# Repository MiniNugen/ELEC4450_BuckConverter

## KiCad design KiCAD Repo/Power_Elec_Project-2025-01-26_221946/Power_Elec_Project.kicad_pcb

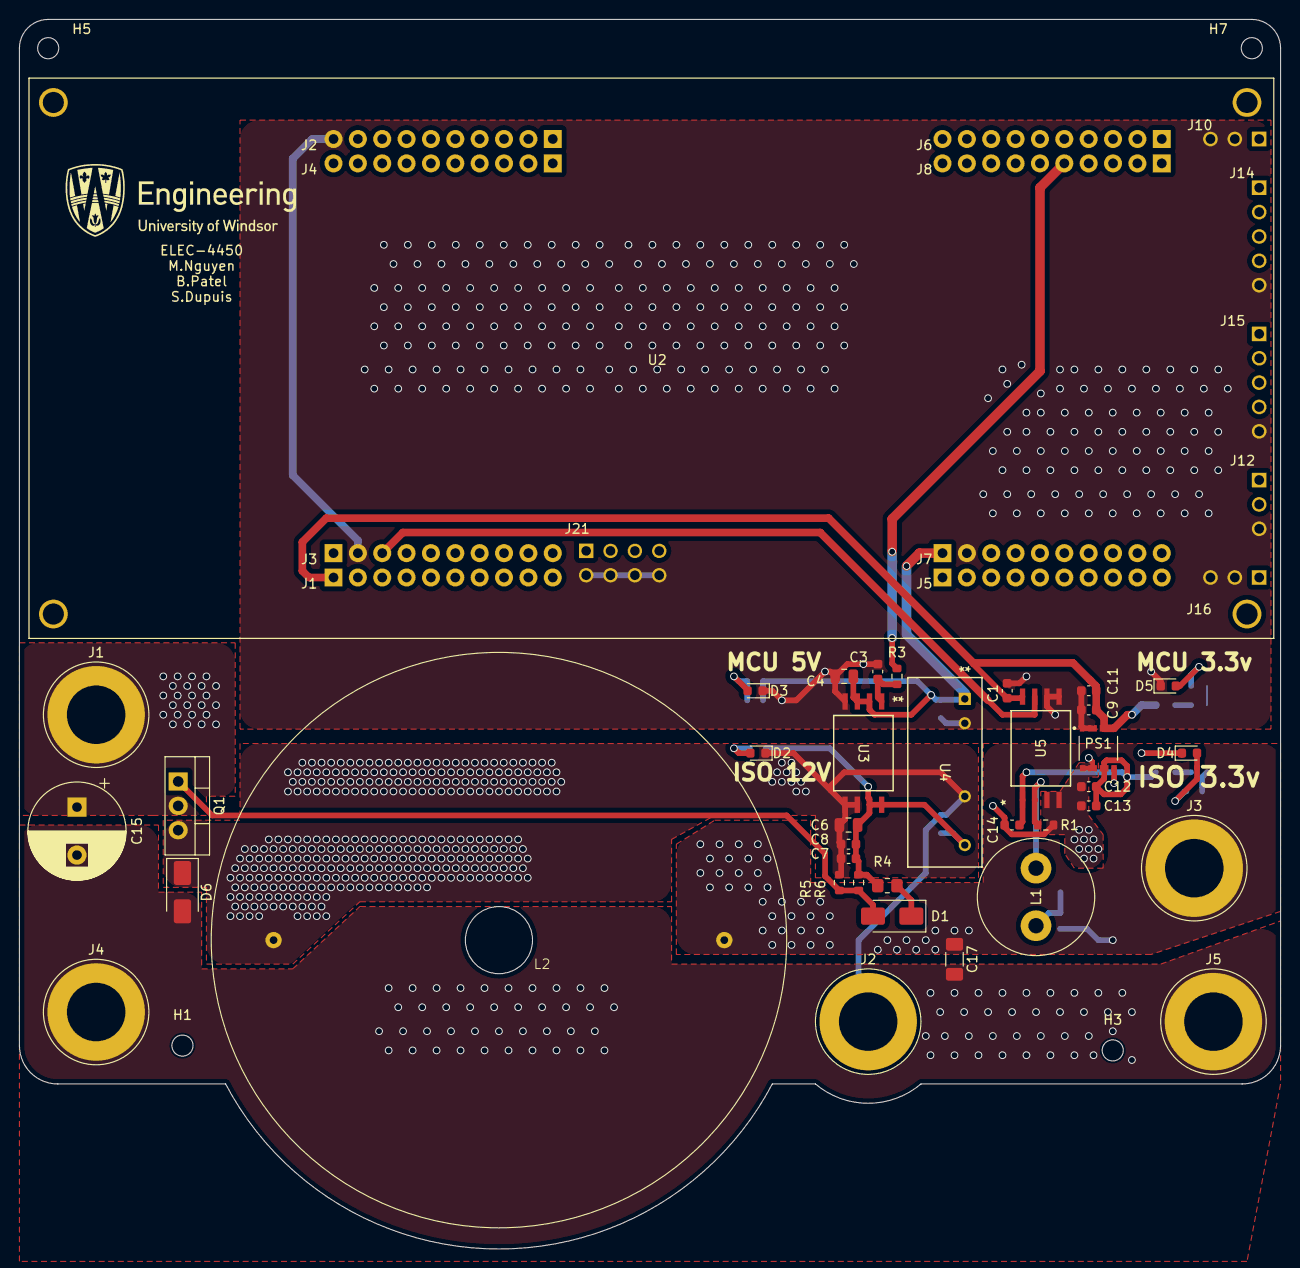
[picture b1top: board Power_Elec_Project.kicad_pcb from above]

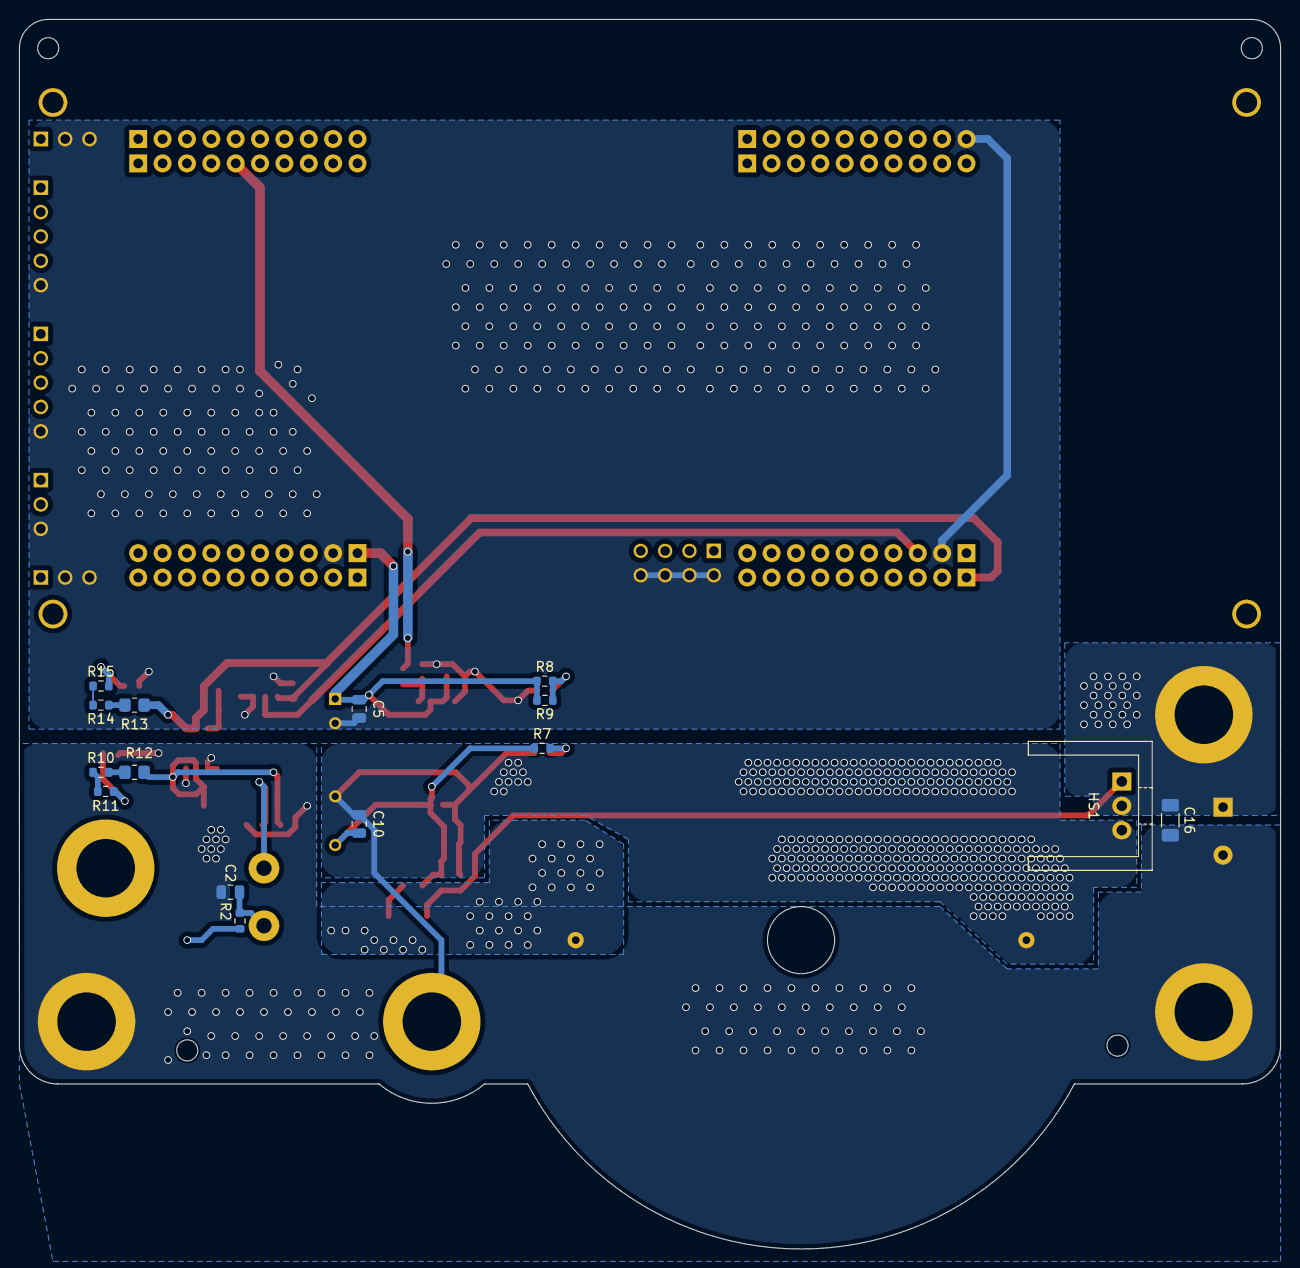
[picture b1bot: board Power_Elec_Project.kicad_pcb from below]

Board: 2 copper layers, 131.5 x 128.2 mm, 56 parts (15 on the bottom side), 24 nets.

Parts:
C1, C9, C12, C14: 0.1uF; C_0603_1608Metric
C2, C5, C10: 1.5 µF; C_0805_2012Metric
C3: 33pF; C_0603_1608Metric
C4, C6: 2.2uF; C_0805_2012Metric
C7, C8, C11: 10uF; C_0603_1608Metric
C13: 22uF; C_0603_1608Metric
C15: 470uF; CP_Radial_D10.0mm_P5.00mm
C16: 1uF; C_1206_3216Metric_Pad1.33x1.80mm_HandSolder
C17: 4.7uF; C_1206_3216Metric_Pad1.33x1.80mm_HandSolder
D1: US2AA; D_SMA
D2: ISO 12V; LED_0603_1608Metric
D3: MCU 5V; LED_0603_1608Metric
D4: ISO 3.3v; LED_0603_1608Metric
D5: MCU 3.3v; LED_0603_1608Metric
D6: SS310; D_SMA
H1, H3, H5, H7: MountingHole; MountingHole_2.2mm_M2
HS1: Heatsink; Heatsink_Stonecold_HS-S03_13.21x12.7mm
J1, J2, J3: RED; Banana_Jack_1Pin
J4, J5: Black; Banana_Jack_1Pin
L1: 18mH; L_Radial_D12.0mm_P6.00mm_Murata_1900R
L2: 68mH; Inductor_Throughhole_Radial; D=60mm, P=47mm
PS1: R05C1TF05S-R; CONV_R05C1TF05S-R
Q1: IRF540N; TO-220-3_Vertical
R1: 165; R_0603_1608Metric
R2: 20.5k; R_0603_1608Metric
R3, R5, R10, R11, R14, R15: 50; R_0603_1608Metric
R4, R12, R13: 12; R_0805_2012Metric_Pad1.20x1.40mm_HandSolder
R6: 7; R_0603_1608Metric
R7, R8, R9: 1.8k; R_0603_1608Metric
U2: LAUNCHXL-F28379D; MOD_LAUNCHXL-F28379D
U3: UCC5304DWVR; SOIC8_DWV_TEX
U4: TMV 0512SHI; TMV-HI_SINGLE_TRP
U5: AMC1300DWVR; DWV8_TEX

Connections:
+3.3V: C1.2, C9.1, C11.1, PS1.4_5 (VIN+), PS1.6 (CTRL), R13.2, U2.J1_1 (3.3V_J1), U5.8 (VDD2)
+5V: C4.1, C5.1, R8.2, R9.2, U2.J7_1 (+5V_J7), U3.2 (VCCI), U3.3 (VCCI), U4.1 (+VIN(VCC))
/PWM: R3.1, U2.J8_5 (GPIO11/PWMOUT6B)
/VFILT: U2.J3_3 (ADCIN14/ANALOGIN), U5.7 (OUTP)
/VG: D1.2 (A), Q1.1 (G), R5.1, R6.2
/VOUT: C17.1, J3.1, L2.2, R2.2
GND: C1.1, C3.2, C4.2, C5.2, C9.2, C11.2, D3.1 (K), D5.1 (K), PS1.1 (VIN-), PS1.2_3 (VIN-__1), U2.J2_10 (GND_J2), U2.J3_2 (GND_J3), U2.J7_2 (GND_J7), U2.J10_2 (GND_J10), U2.J10_3 (GND_J10__1), U2.J12_3 (GND_J12), U2.J14_5 (GND_J14), U2.J15_5 (GND_J15), U2.J16_2 (GND_J16), U2.J16_3 (GND_J16__1), U2.J21_2 (TP21/GND), U2.J21_4 (TP22/GND), U2.J21_6 (TP23/GND), U2.J21_8 (TP24/GND), U3.4 (GND), U4.2 (-VIN(GGND)), U5.5 (GND2), U5.6 (OUTN)
GNDPWR: C2.2, C12.2, C13.2, C14.2, C15.2, C16.2, C17.2, D4.1 (K), D6.2 (A), J4.1, J5.1, PS1.7 (VSEL), PS1.10_11 (VOUT-), PS1.12 (VOUT-__1), R1.2, U5.3 (INN), U5.4 (GND1)
GNDREF: C6.2, C7.2, C8.2, C10.2, D2.1 (K), D6.1 (K), J2.1, L2.1, Q1.3 (S), R5.2, U3.5 (VSS), U3.6 (VSS), U4.5 (-VOUT)
ISO_3.3V: C12.1, C13.1, C14.1, PS1.8_9 (VOUT+), R12.2, U5.1 (VDD1)
ISO_12V: C6.1, C7.1, C8.1, C10.1, R4.1, R6.1, R7.2, U3.7 (OUT), U3.8 (VDD), U4.7 (+VOUT)
unnamed: C2.1, L1.1, R2.1
unnamed: D1.1 (K), R4.2
unnamed: D2.2 (A), R7.1
unnamed: D3.2 (A), R8.1, R9.1
unnamed: D4.2 (A), R11.2
unnamed: D5.2 (A), R15.2
unnamed: R10.1, R12.1
unnamed: R10.2, R11.1
unnamed: R13.1, R14.1
unnamed: R14.2, R15.1
unnamed: C3.1, R3.2, U3.1 (IN)
unnamed: L1.2, R1.1, U5.2 (INP)
VDD: C15.1, C16.1, J1.1, Q1.2 (D)

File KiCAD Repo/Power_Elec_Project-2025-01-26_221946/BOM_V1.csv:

"Reference","Value","Footprint","Qty","MANUFACTURER","Part Number"
"L1","18mH","Inductor_THT:L_Radial_D12.0mm_P6.00mm_Murata_1900R","1","","6100-183K-RC"
"L2","2.2mH","Barrel Inductor AIRD-06-182K:AIRD-06_ABR","1","","AIRD-06-182K"
"U5","AMC1300DWVR","DWV8_TEX","1","","AMC1300DWVR"
"J4,J5","Black","Connector:Banana_Jack_1Pin","2","","BU-P72930-0"
"J1,J2,J3","RED","Connector:Banana_Jack_1Pin","3","","BU-P72930-2"
"C7,C8,C11","10uF","Capacitor_SMD:C_0603_1608Metric","3","","C0603X5R160-106KNP"
"C13","22uF","Capacitor_SMD:C_0603_1608Metric","1","","C0603X5R4R0-226MNE"
"C1,C9,C12,C14","0.1uF","Capacitor_SMD:C_0603_1608Metric","4","","C0603Y5V160-104ZNE"
"C4,C6","2.2uF","Capacitor_SMD:C_0805_2012Metric","2","","C0805X7R160-225MNE"
"C16","1uF","Capacitor_SMD:C_1206_3216Metric_Pad1.33x1.80mm_HandSolder","1","","C1206X7R101-105MNE"
"C3","33pF","Capacitor_SMD:C_0603_1608Metric","1","","C1608NP0330JGTS"
"C2,C5,C10","1.5 µF","Capacitor_SMD:C_0805_2012Metric","3","","CC0805ZRY5V7BB155"
"R2","20.5k","Resistor_SMD:R_0603_1608Metric","1","","CR162052F"
"R4,R12,R13","12","Resistor_SMD:R_0805_2012Metric_Pad1.20x1.40mm_HandSolder","3","","CR0805FB12RS01"
"R3,R5,R10,R11,R14,R15","50","Resistor_SMD:R_0603_1608Metric","6","","CRCW060350R0FKTA"
"R1","165","Resistor_SMD:R_0603_1608Metric","1","","ERJ-3EKF1650V"
"C17","4.7uF","Capacitor_SMD:C_1206_3216Metric_Pad1.33x1.80mm_HandSolder","1","","GRM319R61H475KA12D"
"Q1","IRF540N","Package_TO_SOT_THT:TO-220-3_Vertical","1","","IRF540N"
"U2","LAUNCHXL-F28379D","F28379D:MOD_LAUNCHXL-F28379D","1","Texas Instruments","LAUNCHXL-F28379D"
"PS1","R05C1TF05S-R","R05C1TF05S-R:CONV_R05C1TF05S-R","1","Recom Power","R05C1TF05S-R"
"R6","7","Resistor_SMD:R_0603_1608Metric","1","","RMCF0603FT6R80"
"R7,R8,R9","1.8k","Resistor_SMD:R_0603_1608Metric","3","","RMCF0603JT1K80"
"C15","470uF","Capacitor_THT:CP_Radial_D10.0mm_P5.00mm","1","","RPF1018471M050K"
"D6","SS310","Diode_SMD:D_SMA","1","","SS310"
"U4","TMV 0512SHI","TMV-HI_SINGLE_TRP","1","","TMV 0512SHI"
"U3","UCC5304DWVR","UCC5304DWVR GateDriver_IC:SOIC8_DWV_TEX","1","","UCC5304DWVR"
"D1","US2AA","Diode_SMD:D_SMA","1","","US2AA"
"D2","ISO 12V","LED_SMD:LED_0603_1608Metric","1","","XL-1608UGC-04"
"D3","MCU 5V","LED_SMD:LED_0603_1608Metric","1","","XL-1608UGC-04"
"D4","ISO 3.3v","LED_SMD:LED_0603_1608Metric","1","","XL-1608UGC-04"
"D5","MCU 3.3v","LED_SMD:LED_0603_1608Metric","1","","XL-1608UGC-04"

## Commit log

2025-01-28 Moved Brijal's Schematics To main branch
2025-01-29 Matlab Test
2025-01-29 test
2025-01-29 Matlab
2025-02-17 Added MCU footprint
2025-02-19 LPF design
2025-02-20 Pi LPF simulation
2025-02-20 gate driver import
2025-02-22 PLF and GD circuit
2025-02-22 Push
2025-02-22 PCB layout GD and LPF
2025-02-22 PCB layout
2025-02-24 PCB work and SIMULINK sim
2025-02-24 Simulation
2025-02-24 edited Rin for LPF
2025-02-25 Capacitor change
2025-02-27 BOM added
2025-03-05 calculations
2025-03-08 Inductor and PCB fix
2025-03-09 PCB fix
2025-03-09 Gerber Generation
2025-03-21 Added Name and logo on silkscreen
